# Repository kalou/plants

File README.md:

# Plants
*Plants monitoring and watering*

## Description

Plants is composed of:
* A sensor monitoring system and water pumps controller, written in Python, that
  runs on Linux, likely a Pi:
* Some [hardware](./hw) including a Raspberry Pi hat, switches and sensors.

## Features
### Supported sensors
* Support for ADS1115 ADC, to read voltage level sensors such as standard 555-based capacitive moisture sensors.
* Support for [chirp](https://github.com/Miceuz/i2c-moisture-sensor) i2c sensors, reading temperature and moisture.
### Watering
* Configuration and rule based watering:
  - Triggering watering based on sensor humidity percentage.
  - Watering limits per pump, persisted to disk.
* API to manually trigger watering.
### Metrics
* Export of sensor and pump data metrics to prometheus.
* API to poll running config and basic values.
## Example configuration
```
# Plants configuration

# For prometheus, and API, listen on public interface:
host: 0.0.0.0
port: 9191

# How frequently to poll
poll_interval: 5s

sensor_groups:
  -
    kind: 'chirp'   # Got a chirp for temp metrics
  -
    kind: 'ads1115'
    smbus: 1             # i2c BUS to reach the board, default 1 on rpi
    i2c_address: 72      # Address of the ADS1115
    enable_port: 9       # GPIO turning the group on
    sensors:
      - Dragon tail: &cap_sensor
          voltage_dry: 2.62 # This model has a better oscillator
          voltage_wet: 1.23 # and calibrates differently.
          port: 2
      #- Sensor 1: &bad555_cap_sensor
      #    <<: *cap_sensor
      #    voltage_dry: 2.05  # Than this one, where they used an
      #    voltage_wet: 0.95  # ne555.
      #    port: 2
      - Willows:
          <<: *cap_sensor
          port: 3
      - Small money trees:
          <<: *cap_sensor
          port: 1
      - Pothos:
          <<: *cap_sensor
          port: 0
  -
    kind: 'ads1115'
    smbus: 1             # i2c BUS to reach the board, default 1 on rpi
    i2c_address: 72      # Address of the ADS1115
    enable_port: 11      # GPIO turning the group on
    sensors:
      - Money tree:
          <<: *cap_sensor
          port: 3
      - Lemon tree:
          <<: *cap_sensor
          port: 2
      - Bonsai soil:
          <<: *cap_sensor
          port: 1
      - Parlor palm:
          <<: *cap_sensor
          port: 0

# If configured, pump history is saved across restarts
# in sqlite3 db. Otherwise, in-memory watering limits
# are used.
pumps_history_db: /var/lib/plants/plants_pumps_state.db

pumps:
  - Plants to the left:    # Pump 0
      kind: 'gpio'
      port: 10             # GPIO port activates pump on high
      duration: 20s        # Activate for 20s
      limits: &pump_limits
        - per_interval: 2w
          duration: 40s
        - per_interval: 300s
          duration: 20s
      activation_thresholds:
        - Money tree: 50% 
        - Pothos: 50% 
  - Shelf 1:               # Pump 1
      kind: 'gpio'
      port: 17
      duration: 20s
      limits: *pump_limits
      activation_thresholds:
        - Small money trees: 50%
        - Parlor palm: 50% 
  - Dragon tail:
      kind: 'gpio'         # Pump 2
      port: 22             # GPIO port activates pump on high
      duration: 20s
      limits: *pump_limits
      activation_thresholds:
        - Dragon tail: 50%  
  - Shelf 2:               # Pump 3 
      kind: 'gpio'
      port: 27             # GPIO port activates pump on high
      duration: 20s
      limits: *pump_limits
      activation_thresholds:
        - Lemon tree: 50%
        - Willows: 60%
```

## Developement
### Setup and local experiments
```
bash$ pip install -r requirements.txt
bash$ pip install --editable .
bash$ plants_server -c plants/plants.yaml
```
### Various helpers
```
bash$ python -m unittest discover plants
bash$ black plants # auto format
bash$ pylint plants
```

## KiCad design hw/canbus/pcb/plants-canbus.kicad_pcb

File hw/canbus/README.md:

## Canbus stuff
*Disclaimer: I'm using this project to learn electronics. Use at your own risks and feel free
to reach out with suggestions.*

### Hat
This sensor module is to be used with this [Raspberry Pi hat](../canbus-hat).

### Sensors
Sensors are daisy chained on a low bitrate two-wires BUS
(using CANbus transceiver & protocol, at 20kbps).

Sensor circuit is an attiny85 coupled to an MCP2561.
 * +5v generic sensor + ADC
 * 12v 1A module (e.g. water pump, valve)
 * reset button

### AVR programming and setup
On ubuntu linux:
```
sh$ git submodule init && git submodule update
sh$ sudo apt-get install avrdude avr-libc binutils-avr gcc-avr
sh$ cd avr && make && make avr-install
```

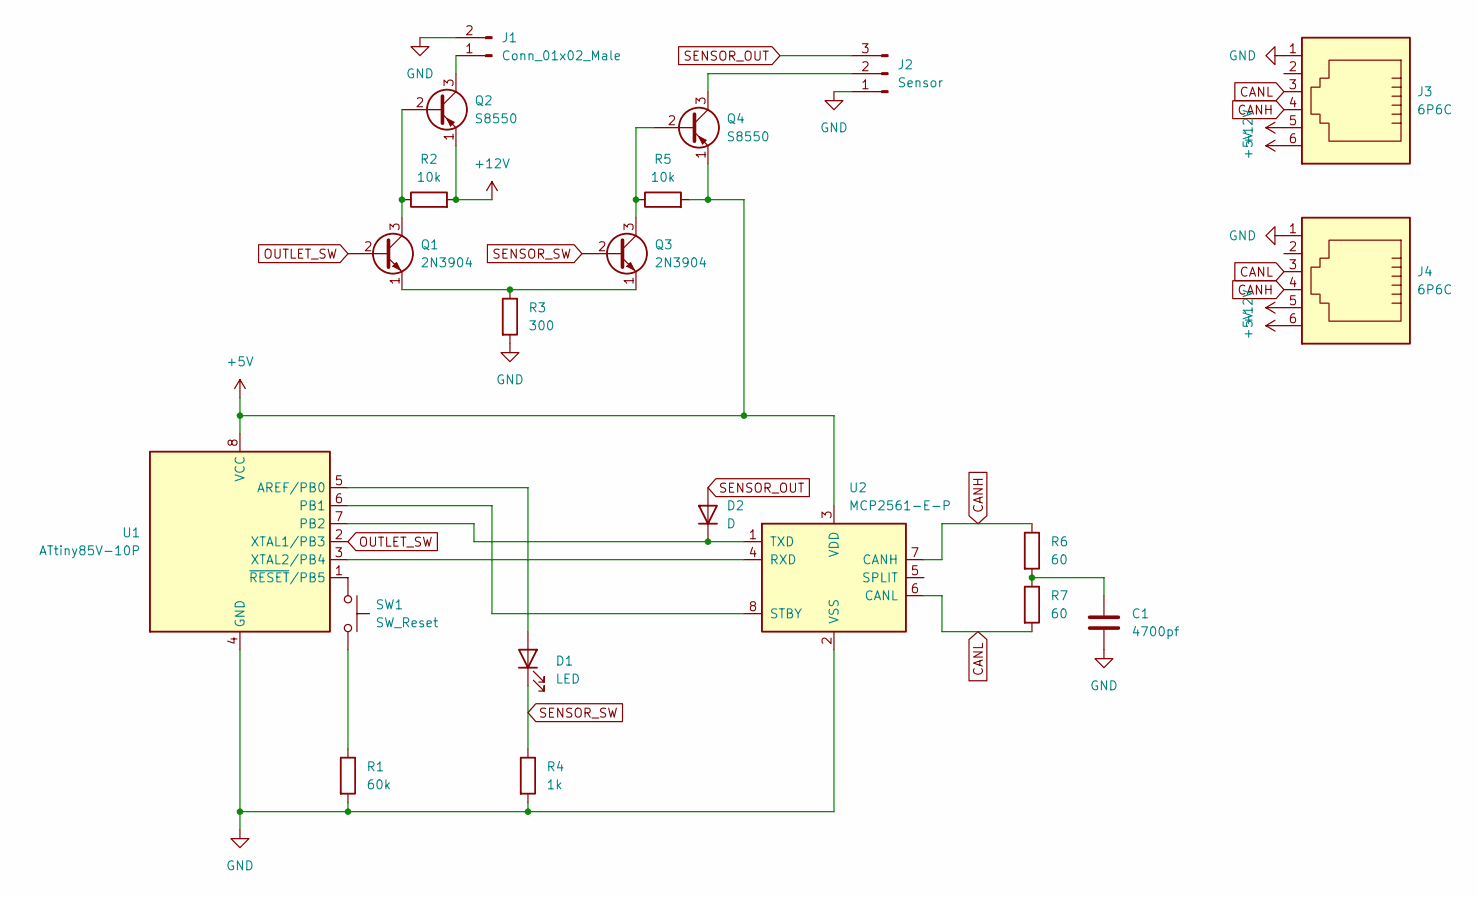
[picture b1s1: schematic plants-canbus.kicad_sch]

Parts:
C1: 4700pf; C_Disc_D4.3mm_W1.9mm_P5.00mm
D1: LED; LED_D1.8mm_W3.3mm_H2.4mm
D2: D; D_DO-35_SOD27_P7.62mm_Horizontal
J1: Conn_01x02_Male; PinHeader_1x02_P2.54mm_Vertical
J2: Sensor; PinHeader_1x03_P2.54mm_Vertical
J3, J4: 6P6C; RJ12_Pulse_E5566
Q1, Q3: 2N3904; TO-92_Inline
Q2, Q4: S8550; TO-92_Inline
R1: 60k; R_Axial_DIN0204_L3.6mm_D1.6mm_P7.62mm_Horizontal
R2, R5: 10k; R_Axial_DIN0204_L3.6mm_D1.6mm_P7.62mm_Horizontal
R3: 300; R_Axial_DIN0204_L3.6mm_D1.6mm_P7.62mm_Horizontal
R4: 1k; R_Axial_DIN0204_L3.6mm_D1.6mm_P7.62mm_Horizontal
R6, R7: 60; R_Axial_DIN0204_L3.6mm_D1.6mm_P7.62mm_Horizontal
SW1: SW_Reset; SW_PUSH_6mm
U1: ATtiny85V-10P; DIP-8_W7.62mm
U2: MCP2561-E-P; DIP-8_W7.62mm

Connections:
+5V: J3.6, J4.6, Q4.1 (E), R5.2, U1.8 (VCC), U2.3 (VDD)
+12V: J3.5, J4.5, Q2.1 (E), R2.2
CANH: J3.4, J4.4, R6.1, U2.7 (CANH)
CANL: J3.3, J4.3, R7.2, U2.6 (CANL)
GND: C1.2, J1.2, J2.1, J3.1, J4.1, R1.2, R3.2, R4.2, U1.4 (GND), U2.2 (VSS)
unnamed: C1.1, R6.2, R7.1
unnamed: D1.2 (A), U1.5 (AREF/PB0)
unnamed: D2.1 (K), U1.7 (PB2), U2.1 (TXD)
unnamed: J1.1, Q2.3 (C)
unnamed: J2.2, Q4.3 (C)
unnamed: Q1.1 (E), Q3.1 (E), R3.1
unnamed: Q1.3 (C), Q2.2 (B), R2.1
unnamed: Q3.3 (C), Q4.2 (B), R5.1
unnamed: R1.1, SW1.2
unnamed: SW1.1, U1.1 (~RESET/PB5)
unnamed: U1.3 (XTAL2/PB4), U2.4 (RXD)
unnamed: U1.6 (PB1), U2.8 (STBY)
OUTLET_SW: Q1.2 (B), U1.2 (XTAL1/PB3)
SENSOR_OUT: D2.2 (A), J2.3
SENSOR_SW: D1.1 (K), Q3.2 (B), R4.1

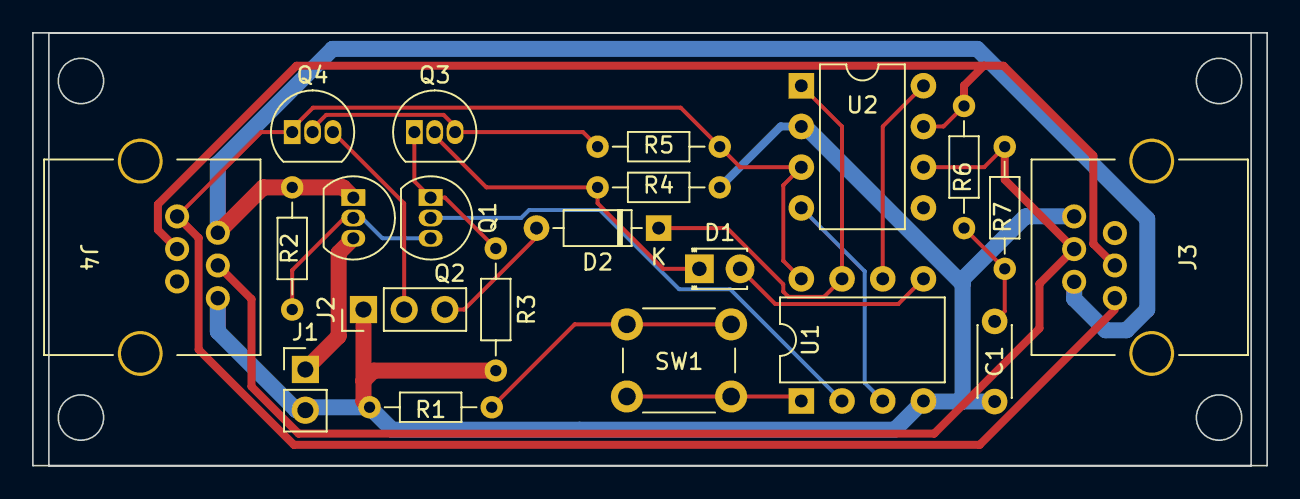
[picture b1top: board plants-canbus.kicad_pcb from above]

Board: 2 copper layers, 77.0 x 27.0 mm, 21 parts (0 on the bottom side), 20 nets.

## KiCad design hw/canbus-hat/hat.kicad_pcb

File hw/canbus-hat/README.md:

# Canbus hat for raspberry Pi
*Disclaimer: I'm using this project to learn electronics. Use at your own risks and feel free
to reach out with suggestions.*

This hat provides +12v power supply to a Raspberry Pi and the CAN bus,
has a few 12v switches for water pumps, and integrates an MCP2515 chip to
enable the Pi to talk on the bus.

## Configuring CAN for the Pi
Uncomment/add these lines to /boot/config.txt:
```
dtparam=spi=on
dtoverlay=mcp2515-can0,oscillator=8000000,interrupt=25
dtoverlay=spi0-hw-cs
```

## Features
 * 1Mb/s MCP2515 + MCP2561 CAN bus hat for Raspberry pi
 * Also powers 4 12v devices w/ GPIO switches (water pumps, ..), spec:
   * Transistors Q{5..8} and polyswitch fuse max current:
     *s8550*: .7A, *ss8550*: 1.5A, mosfets may be an option.
   * current tested setup uses 4.8w (400mA) pumps
 * 12v barrel jack (missing in the above 3d image) powers the pumps and an LM2576
   that provides 5v switched power to the Pi. +5v and +12v are also exported to the
   CAN bus modules via the PS/2 (alternative TBD RJ11) port for use by [the sensors](../canbus).
  * **WARNING** This project does **not** include a security diode on the +5v supply. When +12v
    is connected to the board, **no USB power should be plugged in**.

## Specifics
 * Pumps 0,1,2,3 are activated with GPIO4,GPIO17, GPIO27, GPIO22
   * Output JST pinout is GND,0,1,2,3
 * GPIO GPIO25(22) is connected to INT on the MCP chip. The can module config should
   use `dtoverlay=mcp2515-can0,oscillator=8000000,interrupt=25`.
 * Polyfuse value needs to be adjusted - For 4.8w 240l/h 12v pumps, I use 400mA as it takes
   time to trip it.

### Alternative way to make Pi talk CAN via SPI:
You can also use a ~$3 MCP2515+TJA1050 module with an 8mhz crystal.

Connecting to Pi:
 * GPIO8(24) to CS
 * GPIO10(19) to MOSI
 * GPIO9(21) to MISO
 * GPIO11(23) to SCLK
 * GPIO GPIO25(22) to INT, so the above config works.

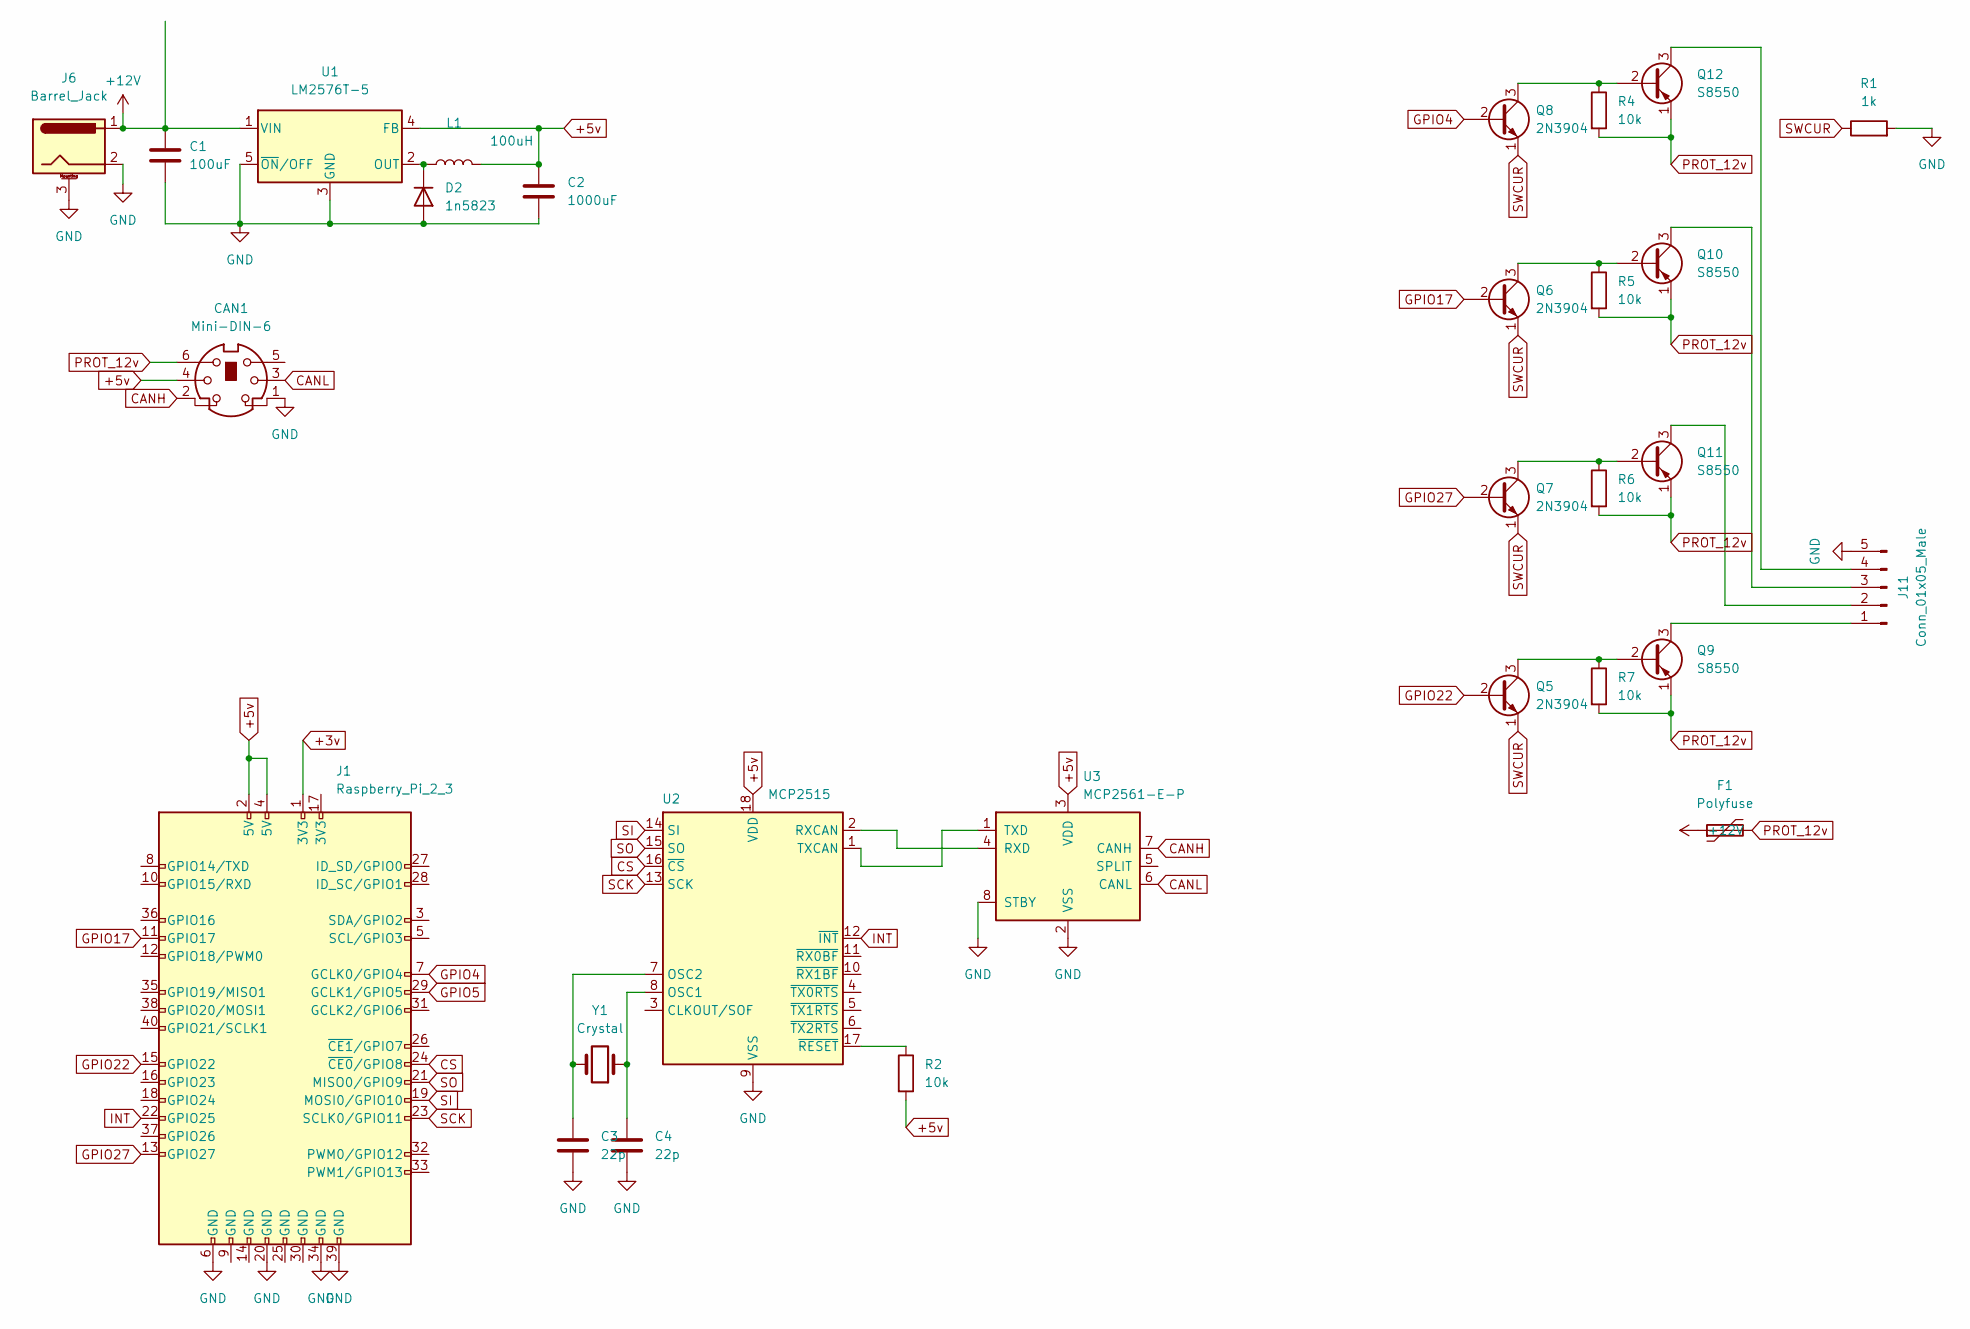
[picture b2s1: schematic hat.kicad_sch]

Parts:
C1: 100uF; CP_Radial_D5.0mm_P2.50mm
C2: 1000uF; CP_Radial_D8.0mm_P2.50mm
C3, C4: 22p; CP_Radial_Tantal_D4.5mm_P2.50mm
CAN1: Mini-DIN-6; Connector_MiniDIN_6
D2: 1n5823; D_DO-201AD_P5.08mm_Vertical_KathodeUp
F1: Polyfuse; Fuse_Littelfuse_395Series
J1: Raspberry_Pi_2_3; PinHeader_2x20_P2.54mm_Vertical
J6: Barrel_Jack; BarrelJack_CUI_PJ-102AH_Horizontal
J11: Conn_01x05_Male; JST_EH_B5B-EH-A_1x05_P2.50mm_Vertical
L1: 100uH; L_Radial_D12.0mm_P10.00mm_Neosid_SD12_style1
Q5, Q6, Q7, Q8: 2N3904; TO-92_Inline
Q9, Q10, Q11, Q12: S8550; TO-92_Inline
R1: 1k; R_Axial_DIN0204_L3.6mm_D1.6mm_P7.62mm_Horizontal
R2, R4, R5, R6, R7: 10k; R_Axial_DIN0204_L3.6mm_D1.6mm_P7.62mm_Horizontal
U1: LM2576T-5; TO-220-5_Vertical
U2: MCP2515; DIP-18_W7.62mm_LongPads
U3: MCP2561-E-P; DIP-8_W7.62mm
Y1: Crystal; Crystal_HC49-U_Vertical

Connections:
+3v: J1.1 (3V3)
+5v: C2.1, CAN1.4, J1.2 (5V), J1.4 (5V), L1.2, R2.2, U1.4 (FB), U2.18 (VDD), U3.3 (VDD)
+12V: C1.1, F1.1, J6.1, U1.1 (VIN)
CANH: CAN1.2, U3.7 (CANH)
CANL: CAN1.3, U3.6 (CANL)
CS: J1.24 (~CE0/GPIO8), U2.16 (~CS)
GND: C1.2, C2.2, C3.2, C4.2, CAN1.1, D2.2 (A), J1.6 (GND), J1.20 (GND), J1.34 (GND), J1.39 (GND), J6.2, J6.3 (MountPin), J11.5, R1.2, U1.3 (GND), U1.5 (~ON/OFF), U2.9 (VSS), U3.2 (VSS), U3.8 (STBY)
GPIO4: J1.7 (GCLK0/GPIO4), Q8.2 (B)
GPIO5: J1.29 (GCLK1/GPIO5)
GPIO17: J1.11 (GPIO17), Q6.2 (B)
GPIO22: J1.15 (GPIO22), Q5.2 (B)
GPIO27: J1.13 (GPIO27), Q7.2 (B)
INT: J1.22 (GPIO25), U2.12 (~INT)
unnamed: C3.1, U2.7 (OSC2), Y1.2
unnamed: C4.1, U2.8 (OSC1), Y1.1
unnamed: D2.1 (K), L1.1, U1.2 (OUT)
unnamed: J11.1, Q9.3 (C)
unnamed: J11.2, Q11.3 (C)
unnamed: J11.3, Q10.3 (C)
unnamed: J11.4, Q12.3 (C)
unnamed: Q5.3 (C), Q9.2 (B), R7.1
unnamed: Q6.3 (C), Q10.2 (B), R5.1
unnamed: Q7.3 (C), Q11.2 (B), R6.1
unnamed: Q8.3 (C), Q12.2 (B), R4.1
unnamed: R2.1, U2.17 (~RESET)
unnamed: U2.1 (TXCAN), U3.1 (TXD)
unnamed: U2.2 (RXCAN), U3.4 (RXD)
PROT_12v: CAN1.6, F1.2, Q9.1 (E), Q10.1 (E), Q11.1 (E), Q12.1 (E), R4.2, R5.2, R6.2, R7.2
SCK: J1.23 (SCLK0/GPIO11), U2.13 (SCK)
SI: J1.19 (MOSI0/GPIO10), U2.14 (SI)
SO: J1.21 (MISO0/GPIO9), U2.15 (SO)
SWCUR: Q5.1 (E), Q6.1 (E), Q7.1 (E), Q8.1 (E), R1.1

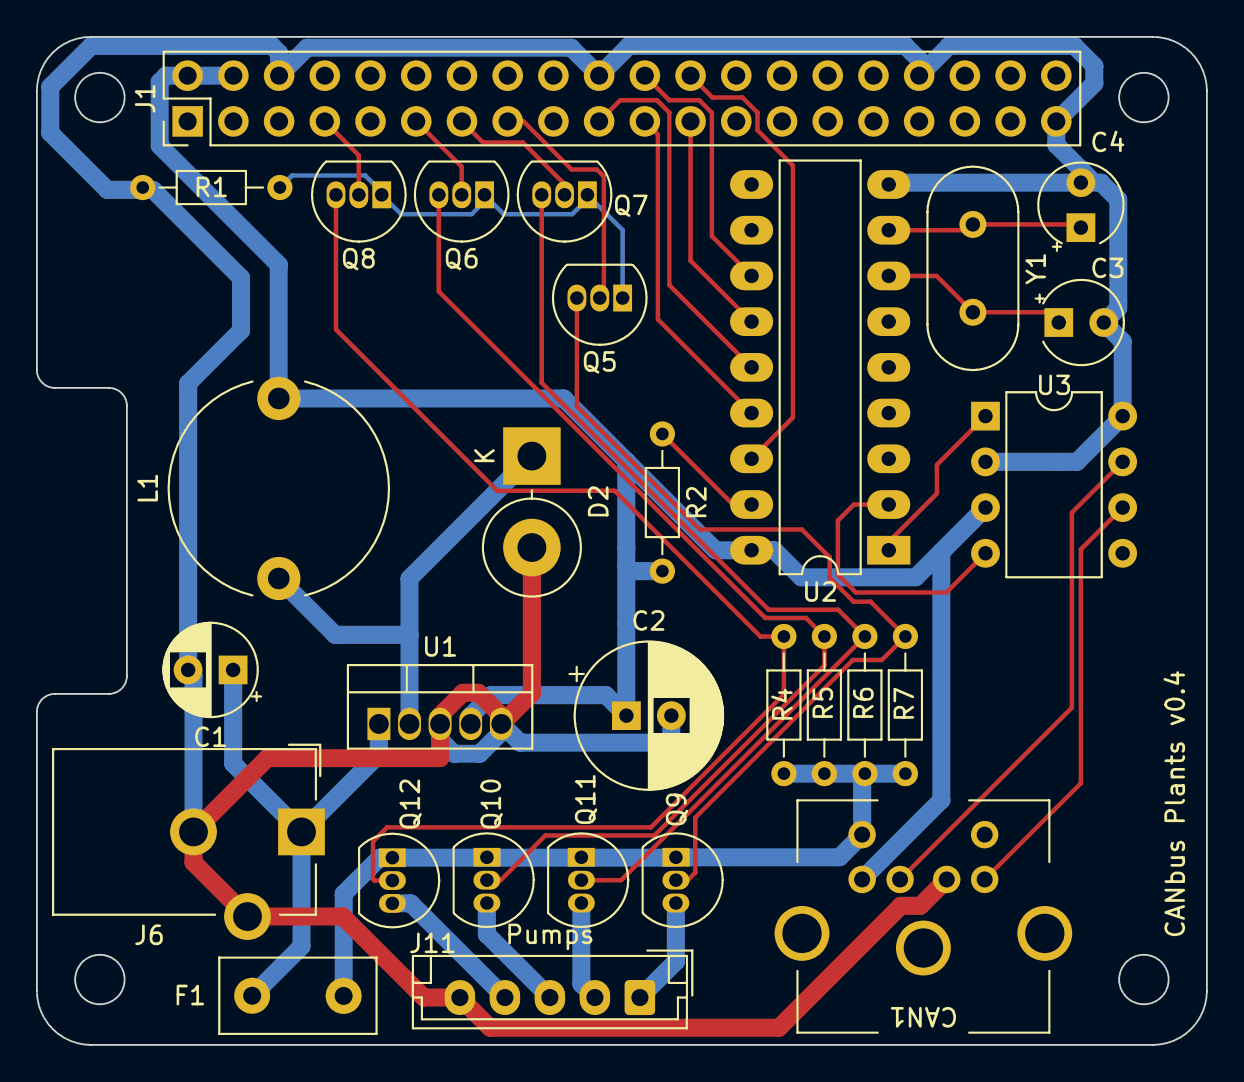
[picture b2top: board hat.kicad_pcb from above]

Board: 2 copper layers, 65.0 x 56.0 mm, 29 parts (0 on the bottom side), 30 nets.

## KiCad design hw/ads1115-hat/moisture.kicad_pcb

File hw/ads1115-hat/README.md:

# Plants hat
*Disclaimer: I'm using this project to learn electronics. Use at your own risks and feel free
to reach out with suggestions.*

## Features
 * i2c ADS1115 ADC (+5v) and 8 sensor ports (pinout +5v,GND,out)
 * re-exports the i2c bus for more advanced sensors
 * powers 4 12v (water pumps, .. devices)
   * Transistors Q{5..8} and polyswitch fuse (also missing in the above 3d image) max current:
     *s8550*: .7A, *ss8550*: 1.5A, mosfets may be an option.
   * current tested setup uses 4.8w (400mA) pumps
 * 12v barrel jack (missing in the above 3d image) powers the pumps and an LM2576 that provides
   5v switched power to the Pi and sensors.
  * **WARNING** This project does **not** include a security diode on the +5v supply. When +12v
    is connected to the board, **no USB power should be plugged in**. Running a
    sensors-only board from USB power leaving the 12v barrel empty
    has not been tested but should work.

## Specifics
 * Sensor ports are divided in two groups of 4
   * Sensors 0,1,2,3 turn on with GPIO11
   * Sensors 4,5,6,7 turn on with GPIO9
   * Data should be read on ADS1115 AIN0,1,2,3
 * Pumps 0,1,2,3 are activated with GPIO17, GPIO27, GPIO22, GPIO10
   * Output JST pinout is GND,0,1,2,3
 * Polyfuse value needs to be adjusted - For 4.8w 240l/h 12v pumps, I use 400mA as it takes
   time to trip it.

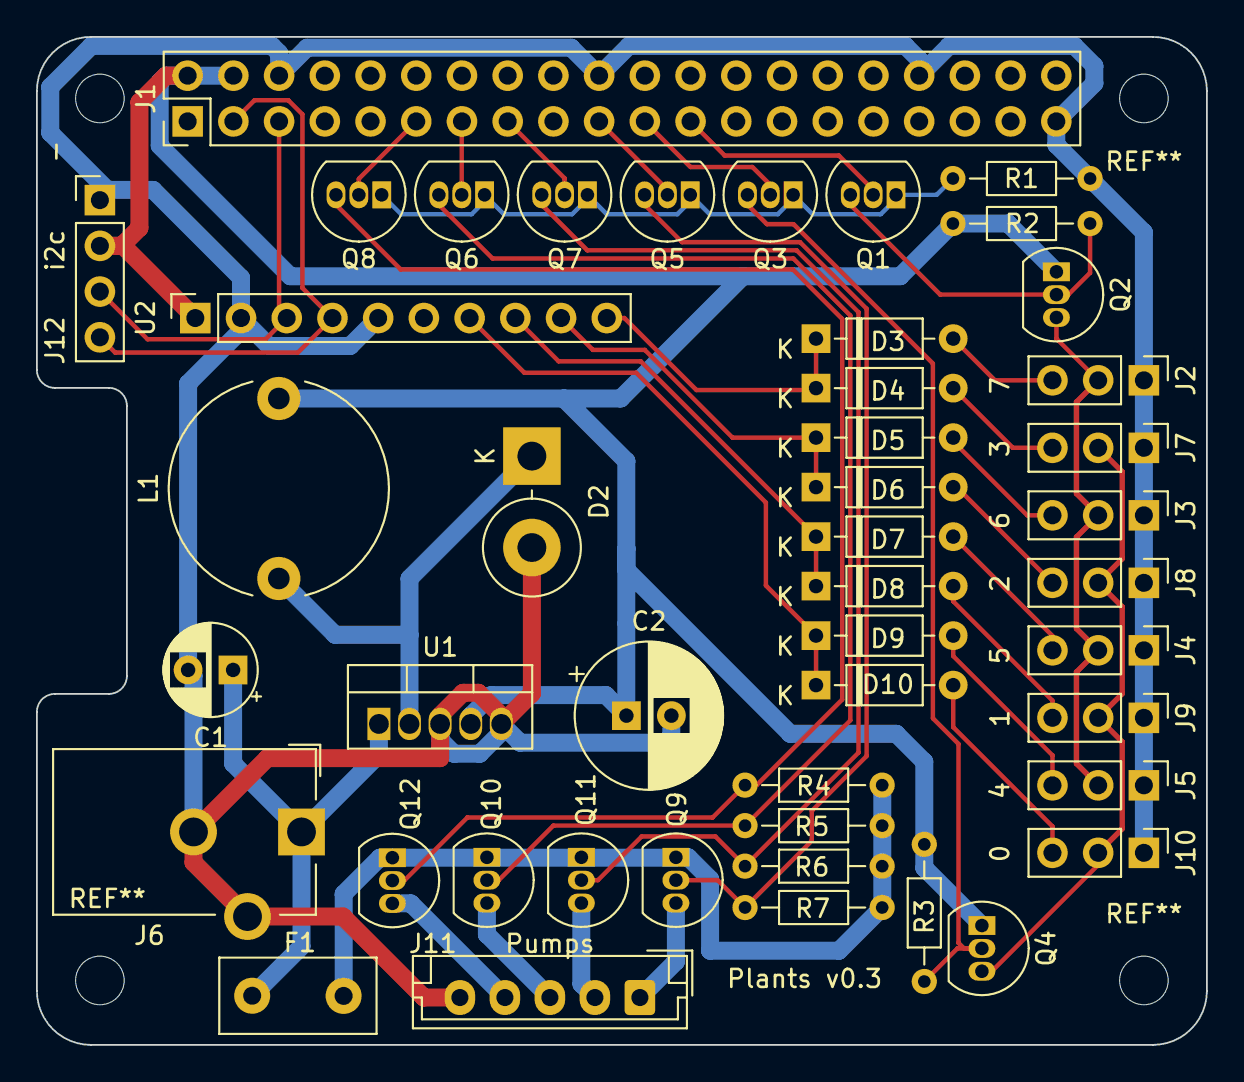
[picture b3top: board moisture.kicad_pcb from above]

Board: 2 copper layers, 65.0 x 56.0 mm, 47 parts (0 on the bottom side), 38 nets.

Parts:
-: MountingHole_2.7mm_M2.5
C1: 100uF; CP_Radial_D5.0mm_P2.50mm
C2: 1000uF; CP_Radial_D8.0mm_P2.50mm
D2: 1n5823; D_DO-201AD_P5.08mm_Vertical_KathodeUp
D3, D4, D5, D6, D7, D8, D9, D10: 1n4148; D_DO-35_SOD27_P7.62mm_Horizontal
F1: Polyfuse; Fuse_Littelfuse_395Series
J1: Raspberry_Pi_2_3; PinHeader_2x20_P2.54mm_Vertical
J2, J3, J4, J5, J7, J8, J9, J10: Sensor; PinHeader_1x03_P2.54mm_Vertical
J6: Barrel_Jack; BarrelJack_CUI_PJ-102AH_Horizontal
J11: Conn_01x05_Male; JST_EH_B5B-EH-A_1x05_P2.50mm_Vertical
J12: Conn_01x04_Male; PinHeader_1x04_P2.54mm_Vertical
L1: 100uH; L_Radial_D12.0mm_P10.00mm_Neosid_SD12_style1
Q1, Q3, Q5, Q6, Q7, Q8: 2N3904; TO-92_Inline
Q2, Q4, Q9, Q10, Q11, Q12: S8550; TO-92_Inline
R1: 1k; R_Axial_DIN0204_L3.6mm_D1.6mm_P7.62mm_Horizontal
R2, R3, R4, R5, R6, R7: 10k; R_Axial_DIN0204_L3.6mm_D1.6mm_P7.62mm_Horizontal
U1: LM2576T-5; TO-220-5_Vertical
U2: ADS1115_devboard; PinSocket_1x10_P2.54mm_Vertical

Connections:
+5v: C2.1, J1.2 (5V), J1.4 (5V), J12.2, L1.2, Q2.1 (E), Q4.1 (E), R2.2, R3.2, U1.4 (FB), U2.1 (vdd)
+12V: C1.1, F1.1, J6.1, U1.1 (VIN)
AIN0: D9.1 (K), D10.1 (K), U2.7 (ain0)
AIN1: D7.1 (K), D8.1 (K), U2.8 (ain1)
AIN2: D5.1 (K), D6.1 (K), U2.9 (ain2)
AIN3: D3.1 (K), D4.1 (K), U2.10 (ain3)
GND: C1.2, C2.2, D2.2 (A), J1.6 (GND), J1.20 (GND), J1.34 (GND), J1.39 (GND), J2.1, J3.1, J4.1, J5.1, J6.2, J6.3 (MountPin), J7.1, J8.1, J9.1, J10.1, J11.5, J12.1, R1.2, U1.3 (GND), U1.5 (~ON/OFF), U2.2 (gnd), U2.5 (addr)
GPIO9: J1.21 (MISO0/GPIO9), Q3.2 (B)
GPIO10: J1.19 (MOSI0/GPIO10), Q5.2 (B)
GPIO11: J1.23 (SCLK0/GPIO11), Q1.2 (B)
GPIO17: J1.11 (GPIO17), Q8.2 (B)
GPIO22: J1.15 (GPIO22), Q7.2 (B)
GPIO27: J1.13 (GPIO27), Q6.2 (B)
unnamed: D2.1 (K), L1.1, U1.2 (OUT)
unnamed: D3.2 (A), J2.3
unnamed: D4.2 (A), J7.3
unnamed: D5.2 (A), J3.3
unnamed: D6.2 (A), J8.3
unnamed: D7.2 (A), J4.3
unnamed: D8.2 (A), J9.3
unnamed: D9.2 (A), J5.3
unnamed: D10.2 (A), J10.3
unnamed: J2.2, J3.2, J4.2, J5.2, Q2.3 (C)
unnamed: J7.2, J8.2, J9.2, J10.2, Q4.3 (C)
unnamed: J11.1, Q9.3 (C)
unnamed: J11.2, Q11.3 (C)
unnamed: J11.3, Q10.3 (C)
unnamed: J11.4, Q12.3 (C)
unnamed: Q1.3 (C), Q2.2 (B), R2.1
unnamed: Q3.3 (C), Q4.2 (B), R3.1
unnamed: Q5.3 (C), Q9.2 (B), R7.1
unnamed: Q6.3 (C), Q10.2 (B), R5.1
unnamed: Q7.3 (C), Q11.2 (B), R6.1
unnamed: Q8.3 (C), Q12.2 (B), R4.1
PROT_12v: F1.2, Q9.1 (E), Q10.1 (E), Q11.1 (E), Q12.1 (E), R4.2, R5.2, R6.2, R7.2
SCL: J1.5 (SCL/GPIO3), J12.3, U2.3 (scl)
SDA: J1.3 (SDA/GPIO2), J12.4, U2.4 (sda)
SWCUR: Q1.1 (E), Q3.1 (E), Q5.1 (E), Q6.1 (E), Q7.1 (E), Q8.1 (E), R1.1

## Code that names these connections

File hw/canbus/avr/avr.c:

#include <avr/io.h>
#include <avr/interrupt.h>
#include <avr/sleep.h>

#include "can.h"
#include "plants.h"

// PB0, PDIP pin 5 turns on transistor to sensor's +5v.
// The sensor output is measured at ADC PB1 (ADC1), which
// is also the pin used for CAN transceiver TX by canbus.
#define DD_SENSOR_VCC (1 << DDB0)
#define P_SENSOR_VCC (1 << PB0)
#define SENSOR_on() do { PORTB |= P_SENSOR_VCC; } while(0)
#define SENSOR_off() do { PORTB &= ~P_SENSOR_VCC; } while(0)

#define DD_SWITCH_VCC (1 << DDB3)
#define P_SWITCH_VCC (1 << PB3)
#define SWITCH_on() do {  PORTB |= P_SWITCH_VCC; } while(0)
#define SWITCH_off() do {  PORTB &= ~P_SWITCH_VCC; } while(0)


static volatile bool adc_complete = false;
ISR(ADC_vect)
{
	adc_complete = true;
}

int16_t read_adc(int adc)
{
	int16_t reading, avg=0;

	/* Enable sleep mode, with ADC noise reduction,
	 * enable ADC and the ADC completion interrupt.
	 */
	MCUCR = (1<<SE) | (1<<SM0); 

	if (adc == 15) {
		// For temperature reading:
		// MUX[3:0] = 0b1111 selecting ADC4
		// REFS[2:0] = 0b010 selecting internal 1.1v ref
		ADMUX = (1<<REFS1) | 15;
	} else {
		// MUX[3:0] = 0b001, ADC1 (PB2)
		// REFS[2:0] = 0b000, Vcc reference
		ADMUX = adc & 3;
	}
	ADCSRA = (1<<ADEN) | (1<<ADIE) | (1<<ADIF) | 7; // Enable ADC, with interrupt, prescaler: ~60khz

	sei();

	// Perform moving average over 16 readings.
	for (int i = 0; i <16; i++) {
		adc_complete = false;
		sleep_cpu();
		while(!adc_complete);

		reading = ADCL;
		reading |= ADCH << 8;

		if (i == 0)
			continue;
		else if (i == 1)
			avg = reading;
		else
			avg = avg + ((reading - avg) / (i+1));
	}

	// disable ADC to save power
	ADCSRA &= ~(1<<ADEN);

	return avg;
}

uint16_t read_temperature()
{
	return read_adc(15);
}

uint16_t read_sensor()
{
	SENSOR_on();
	// Disable transceiver and set TXD low for measure.
	STBY_high();
	DDRB &= ~(1<<DD_TXD);
	TXD_low();

	// Give sensor some warmup delay before we measure it.
	can_delay_ms(500);

	uint16_t v = read_adc(1);

	// Restore TXD & transceiver.
	SENSOR_off();
	TXD_high();
	DDRB |= (1<<DD_TXD);
	STBY_low();

	return v;
}

/* To turn RST port into a button without having
 * to reprogram the fuse, we use a well-known
 * divider trick.
 *
 * From datasheet R-rst is a pullup between 30k & 60k.
 * With a ~47k resistor to GND, ADC0 should read
 * somewhere between 400 and 700.
 */
bool is_button()
{
	uint16_t v = read_adc(0);
	return (v > 350 && v < 750);
}

bool check_reset_sequence()
{
	uint8_t cnt = 0;
	do {
		// Signal that we detect it
		if (is_button() && (cnt%20 == 0)) {
			SENSOR_on();
			can_delay_ms(100);
			SENSOR_off();
		}
		if (cnt++ > 200)
			return true;
	} while(is_button());
	return false;
}

void save_config(plants_config_t *conf)
{
	conf->crc = 0;
	conf->crc = compute_crc(conf, sizeof(conf));

	EECR = (0<<EEPM1)|(0<<EEPM0);
	for (int i = 0; i < sizeof(plants_config_t); i++) {
		EEAR = i;
		EEDR = *((char *) conf+i);
		EECR |= (1<<EEMPE);
		EECR |= (1<<EEPE);

		while (EECR & (1<<EEPE));
	}
}

bool load_config(plants_config_t *conf)
{
	char *p = (char *) conf;
	uint16_t crc;

	for (int i=0; i < sizeof(plants_config_t); i++) {
		EEAR = i;
		EECR |= (1<<EERE);
		*p++ = EEDR;
	}

	crc = conf->crc;
	conf->crc = 0;
	if (compute_crc(conf, sizeof(conf)) == crc)
		return true;
	return false;
}

void perform_reconfig(plants_config_t *conf)
{
	int attempt = 0;
	can_header_t *c;

	for(;;) {
		// Shortly enable sensor to signal reset via LED.
		SENSOR_on();
		if (!(attempt++ % 5))
			can_request(PLANTS_AUTOCONF_ID, 0);
		c = can_receive(200);
		SENSOR_off();
		if (c && c->id == PLANTS_AUTOCONF_ID && !c->rtr) {
			// This contains our ID
			conf->id = *((uint32_t *) c->data) & 0x1fffffff;
			// Attempt to publish to it. If we get an
			// ACK, we own it.
			if (can_send(conf->id, "random", 6) == 0) {
				save_config(conf);
				return;
			}
		}
	}
}

int main(void)
{
	plants_config_t conf;

	DDRB = DD_SENSOR_VCC | DD_SWITCH_VCC;

	// Disable digital input on TX and RST, used as ADC
	DIDR0 = (1<<ADC1D) | (1<<ADC0D);

	// Tiny power savings. Most savings
	// are done by sleeping.
	PRR |= (1<<PRTIM1) | (1<<PRUSI);

	can_init();

	// Read sensor at boot to indicate firmware startup.
	read_sensor();

	if (!load_config(&conf)) {
		can_send(0x123, (char *) &conf, sizeof(conf));
		perform_reconfig(&conf);
	}

	for (;;) {
		can_header_t *c;

		do {
			c = can_receive(500);
			if (check_reset_sequence()) {
				DEBUG_high();
				perform_reconfig(&conf);
				DEBUG_low();
			}
		} while(!c);


		if ((c->id == conf.id) || (c->id == PLANTS_ALL_SENSORS_ID)) {
			if (c->rtr) {
				uint16_t sensor_data = read_sensor();
				can_send(conf.id, (char *)&sensor_data, 2);
			} else if (c->len == 2 && c->data[0] == PLANTS_CMD_SWITCH) {
				switch(c->data[1]) {
					case PLANTS_CMD_SWITCH_ON:
						if (c->id == conf.id)
							SWITCH_on();
						break;
					case PLANTS_CMD_SWITCH_OFF:
						SWITCH_off();
						break;
				}
			}
		}
	}
}

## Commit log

2023-11-24 initial
2023-11-24 lint setup.py
2023-11-24 fix "Multiple top-level packages discovered in a flat-layout"
2023-11-24 relint setup.py
2024-01-07 Proto for ATtiny85 CAN sensors+switches
2024-01-07 Sync tinycan commit
2024-01-17 Replace PS/2 connector with RJ12
2024-09-22 CANbus Raspberry Pi hat
    Raspberry Pi hat with 12v power supply, 4 12v/1a outputs, CANbus port (MCP2515+MCP2561)
2024-09-22 fix missing cuts for corner holes
2024-09-22 Make sensors passive, rather than noisy
    Mostly, reading sensor data is done w/ RTR frames. Other small changes.
